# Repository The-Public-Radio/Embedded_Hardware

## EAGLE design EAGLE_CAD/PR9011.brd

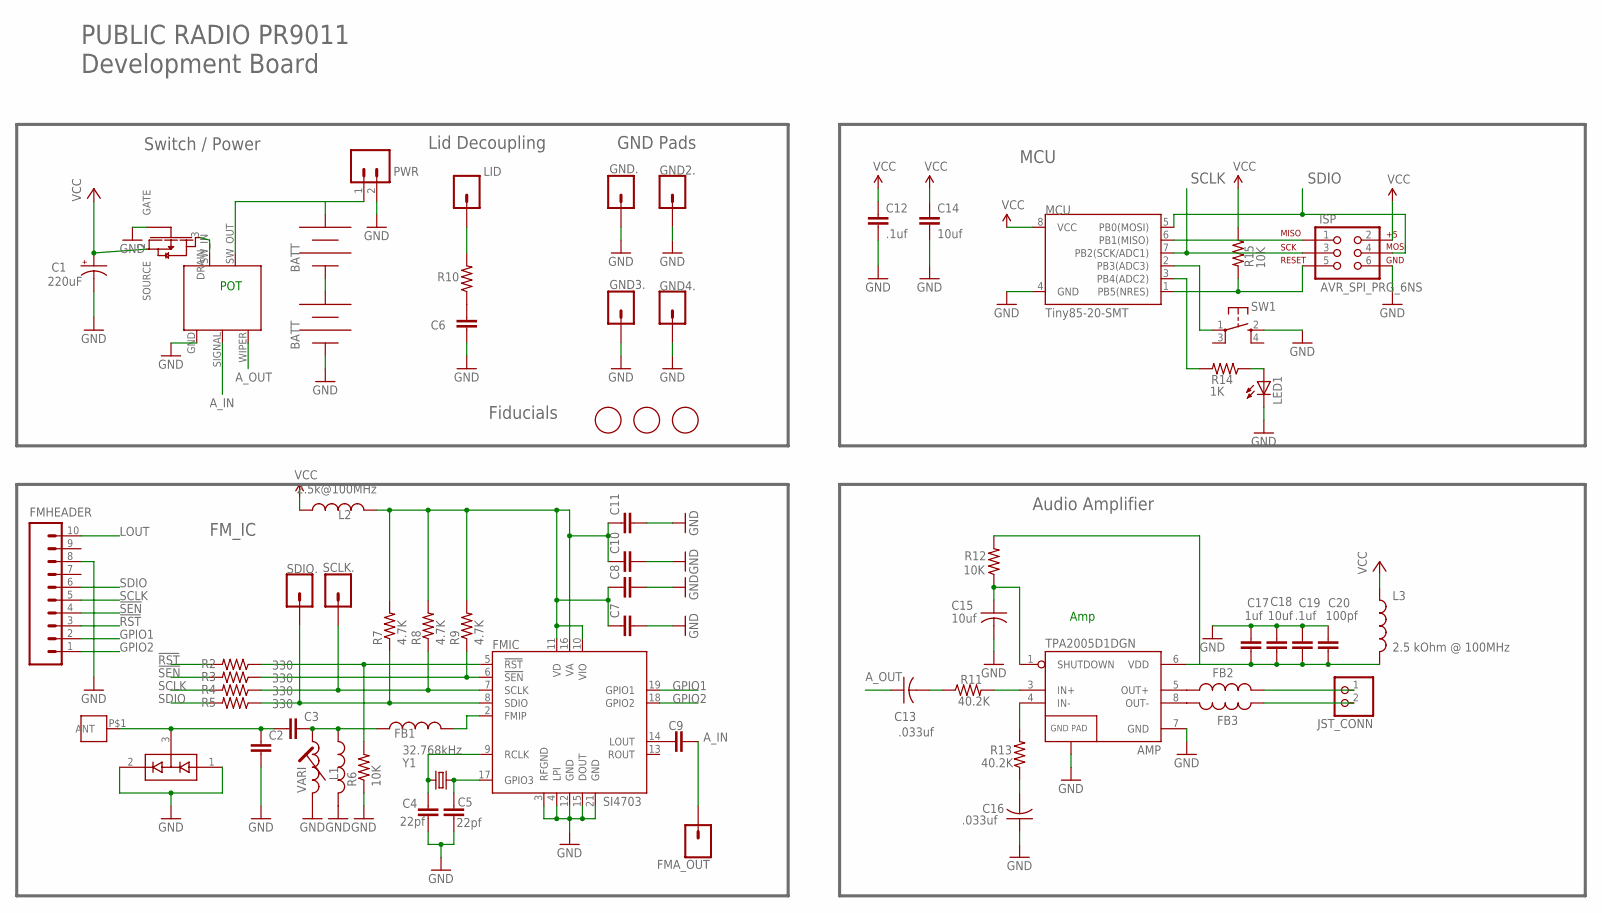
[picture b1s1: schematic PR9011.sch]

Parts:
AMP: TPA2005D1DGN; POWER-SOP8
C1: 220uF; PANASONIC_C
C2, C3, C7, C9: 1.0uF; 0805
C4, C5: 22pf; 0805
C6: CAP0805; 0805
C8: .1uF; 0805
C10: 22nF; 0805
C11: 4.7uF; 0805
C12, C19: .1uf; 0805
C13, C16: .033uf; C0603
C14, C18: 10uf; 0805
C15: 10uf; C0603
C17: 1uf; 0805
C20: 100pf; 0805
D1: BAV99; SOT23-3
FB1, FB2, FB3: INDUCTOR0805; 0805
FET1: SI2333DDS
FMA_OUT: M01PTH; 1X01
FMHEADER: M10LOCK; 1X10_LOCK
FMIC: SI4703; SPARKFUN_SI470X
GND2., GND3., GND4., GND.: M01PTH; 1X01
ISP: AVR_SPI_PRG_6NS; 2X3-NS
J1: M3_SCREW_POST
JP5, JP6: BK-92_MPD_AA_BATT_CLIP
JST_CONN: JST_2PIN-SMT-RA; JST-PH-2-SMT-RA
L1: INDUCTOR0805; 0805
L2: 2.5k@100MHz; 0603
L3: 2.5 kOhm @ 100MHz; 0603
LED1: LEDSML0603; SML0603
LID: M01PTH; 1X01
MCU: Tiny85-20-SMT; SO08-EIAJ
PWR: M02PTH3; 1X02_LONGPADS
R1: RV170SF_TAIWANA_POT_SW
R2, R3, R4, R5: 330; 0805
R6: 10K; 0805
R7, R8, R9: 4.7K; 0805
R10: RESISTOR0805-RES; 0805
R11, R13: 40.2K; R0603
R12, R15: 10K; R0603
R14: 1K; R0603
SCLK.: M01PTH; 1X01
SDIO.: M01PTH; 1X01
SW1: SPST_TACT-KMR2; KMR2
U$1, U$2, U$4: FIDUCIAL; FIDUCIAL_1MM
VARI: L-TRIM; 146/150
Y1: 32.768kHz; CRYSTAL-32KHZ-SMD

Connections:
3.3V: C7.1, C8.1, C10.1, C11.1, FMIC.10 (VIO), FMIC.11 (VD), FMIC.16 (VA), L2.2, R7.2, R8.2, R9.2
!RST-L: FMIC.5 (!RST), R2.1, R6.2
!SEN: FMHEADER.4, R3.2
!SEN-L: FMIC.6 (!SEN), R3.1, R9.1
A_IN: C9.2, FMA_OUT.1, R1.SIGNAL
A_OUT: C13.1, R1.WIPER
GND: AMP.7 (GND), AMP.9 (GND), C1.-, C2.2, C4.2, C5.2, C6.2, C7.2, C8.2, C10.2, C11.2, C12.2, C14.2, C15.2, C16.1, C17.1, C18.1, C19.1, C20.1, D1.1 (A1), D1.2 (C2), FET1.1 (GATE), FMHEADER.8, FMIC.3 (RFGND), FMIC.4 (LPI), FMIC.12 (GND), FMIC.15 (DOUT), FMIC.21 (GND), GND2..1, GND3..1, GND4..1, GND..1, ISP.6, JP6.NEG, JP6.NEG@2 (NEG), L1.2, LED1.C, MCU.4 (GND), PWR.2, R1.GND, R6.1, SW1.2 (S), VARI.P$1 (START)
GPIO1: FMHEADER.2, FMIC.19 (GPIO1)
GPIO2: FMHEADER.1, FMIC.18 (GPIO2)
LOUT: C9.1, FMHEADER.10, FMIC.14 (LOUT)
unnamed: C4.1, FMIC.9 (RCLK), Y1.X2 (2)
unnamed: C5.1, FMIC.17 (GPIO3), Y1.X1 (1)
unnamed: C13.2, R11.1
unnamed: AMP.3 (IN+), R11.2
unnamed: AMP.4 (IN-), R13.2
unnamed: FB1.2, FMIC.2 (FMIP)
unnamed: LED1.A, R14.1
unnamed: LID.1, R10.2
unnamed: FB2.2, JST_CONN.1 (2)
unnamed: MCU.2 (PB3(ADC3)), SW1.1
unnamed: MCU.3 (PB4(ADC2)), R14.2
unnamed: JP5.NEG, JP5.NEG@2 (NEG), JP6.POS, JP6.POS@2 (POS)
unnamed: C2.1, C3.1, D1.3 (COM), J1.P$1
unnamed: JP5.POS, JP5.POS@2 (POS), PWR.1, R1.SW_OUT
unnamed: C3.2, FB1.1, L1.1, VARI.P$2 (END)
unnamed: AMP.8 (OUT-), FB3.2
unnamed: AMP.6 (VDD), C17.2, C18.2, C19.2, C20.2, L3.2, R12.2
unnamed: AMP.5 (OUT+), FB2.1
unnamed: AMP.1 (SHUTDOWN), C15.1, R12.1
unnamed: C16.2, R13.1
unnamed: FET1.3 (DRAIN), R1.SW_IN
unnamed: C6.1, R10.1
OUT-: FB3.1, JST_CONN.2 (1)
PB5: ISP.5, MCU.1 (PB5(NRES)), R15.2
SCLK: FMHEADER.5, ISP.3, MCU.7 (PB2(SCK/ADC1)), R4.2
SCLK-L: FMIC.7 (SCLK), R4.1, R8.1, SCLK..1
SDIO: FMHEADER.6, ISP.4, MCU.5 (PB0(MOSI)), R5.2
SDIO-L: FMIC.8 (SDIO), R5.1, R7.1, SDIO..1
VCC: C1.+, C12.1, C14.1, FET1.2 (SOURCE), ISP.2, L2.1, L3.1, MCU.8 (VCC), R15.1

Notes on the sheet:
Amp
POT
FM_IC
Switch / Power
Lid Decoupling
Audio Amplifier
MCU
PUBLIC RADIO PR9011 Development Board
GND Pads
Fiducials

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
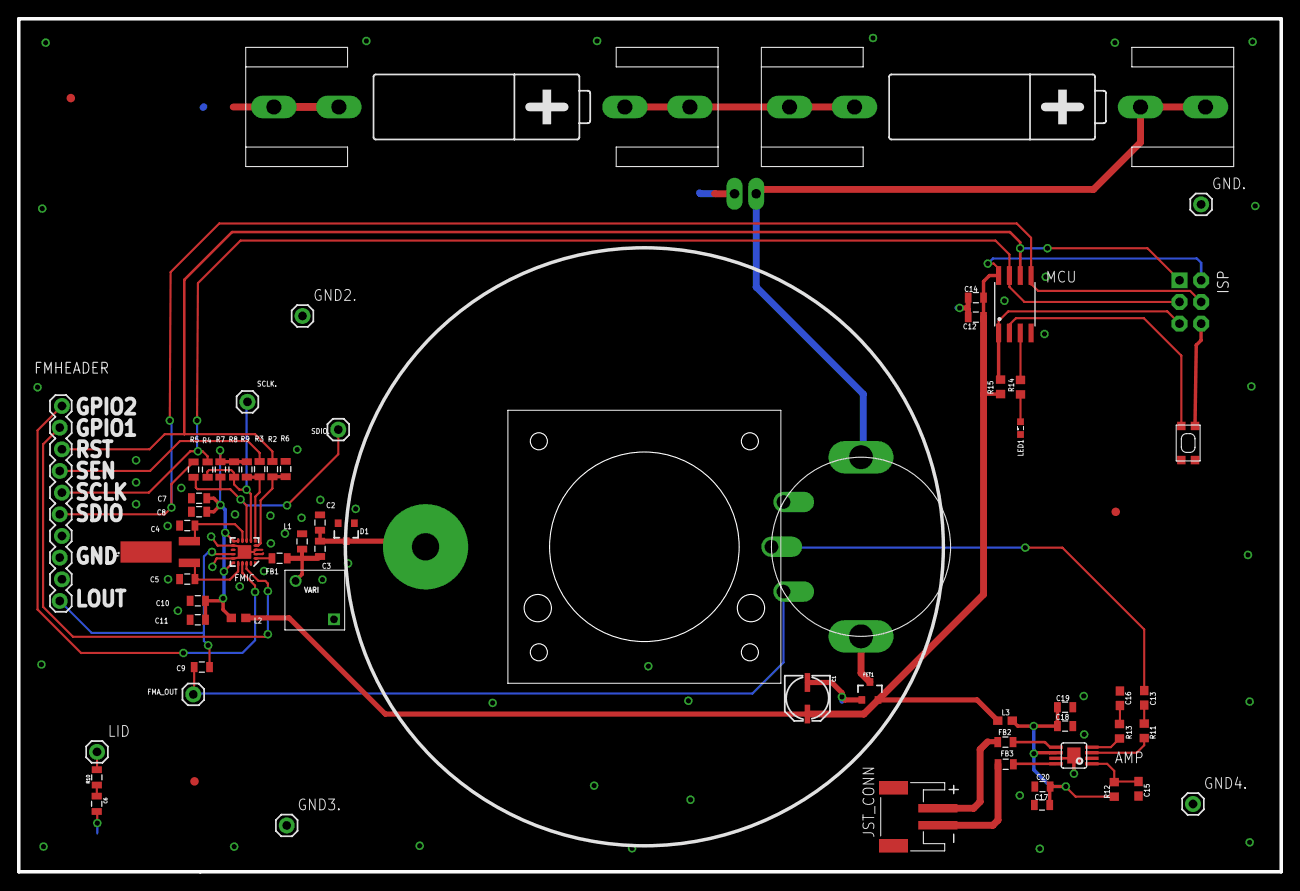
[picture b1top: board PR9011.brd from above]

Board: 2 copper layers, 148.0 x 100.0 mm, 69 parts (0 on the bottom side), 40 nets.

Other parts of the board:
SPEAKER: CE32A_FOR_JST

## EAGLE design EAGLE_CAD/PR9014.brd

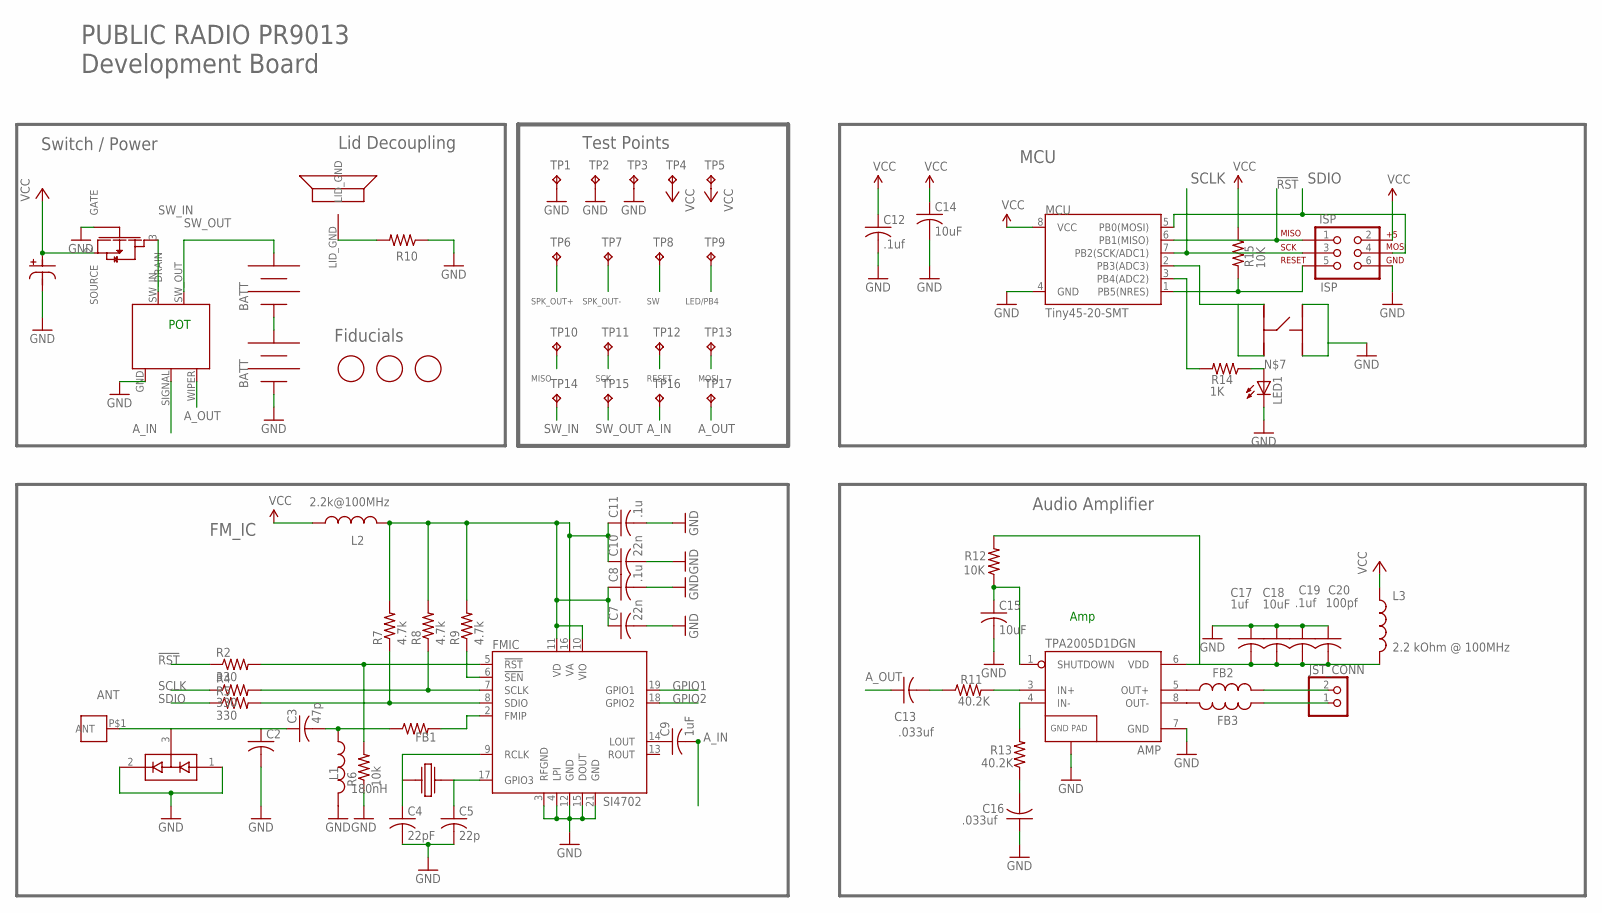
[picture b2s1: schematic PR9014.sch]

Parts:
AMP: TPA2005D1DGN; POWER-SOP8
C1: 220uF; NICHICON_SERIESUD
C2: C-USC0402; C0402
C3: 47p; C0402
C4: 22pF; C0402
C5: 22p; C0402
C7, C10: 22n; C0402
C8, C11: .1u; C0402
C9: 1uF; C0402
C12, C19: .1uf; C0402
C13, C16: .033uf; C0402
C14, C15, C18: 10uF; C0603
C17: 1uf; C0402
C20: 100pf; C0402
D1: BAV99; SOT23
FB1: R-US_R0402; R0402
FB2, FB3: INDUCTOR0805; 0805
FET2: AO3435
FMIC: SI4702; SI470X
ISP: ISP; 2X3-NS
J1: M3_SCREW_POST
JP5, JP6: BK-92_MPD_AA_BATT_CLIP
JST_CONN: JST_2PIN-SMT-RA; JST-PH-2-SMT-RA
L1: 180nH; 0805
L2: 2.2k@100MHz; C0402
L3: 2.2 kOhm @ 100MHz; C0402
LED1: LEDSML0603; SML0603
MCU: Tiny45-20-SMT; SO08-EIAJ
R1: RV170SF_TAIWANA_POT_SW
R2, R4, R5: 330; R0402
R6: 10k; R0402
R7, R8, R9: 4.7k; R0402
R10: R-US_R0805; R0805
R11, R13: 40.2K; R0402
R12, R15: 10K; R0402
R14: 1K; R0402
SW1: C&K_PTS645; C&K_TACTILE_SWITCH
TP1, TP2, TP3, TP4, TP5, TP6, TP7, TP8, TP9, TP10, TP11, TP12, TP13, TP14, TP15, TP16, TP17: TPTP20R; TP20R
U$1: CE32A_FOR_JST
U$3, U$4, U$5: FIDUCIAL; FIDUCIAL_1MM
U$6: ABS25XTAL

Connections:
3.3V: C7.1, C8.1, C10.1, C11.1, FMIC.10 (VIO), FMIC.11 (VD), FMIC.16 (VA), L2.2, R7.2, R8.2, R9.2
!RST: ISP.1, MCU.6 (PB1(MISO)), R2.1, TP10.TP
!RST-L: FMIC.5 (!RST), R2.2, R6.2
!SEN-L: FMIC.6 (!SEN), R9.1
ANT: C2.1, C3.1, D1.3 (COM), J1.P$1
A_IN: C9.2, R1.SIGNAL, TP16.TP
A_OUT: C13.1, R1.WIPER, TP17.TP
GND: AMP.7 (GND), AMP.9 (GND), C1.P$2, C2.2, C4.2, C5.2, C7.2, C8.2, C10.2, C11.2, C12.2, C14.2, C15.2, C16.1, C17.1, C18.1, C19.1, C20.1, D1.1 (A1), D1.2 (C2), FET2.1 (GATE), FMIC.3 (RFGND), FMIC.4 (LPI), FMIC.12 (GND), FMIC.15 (DOUT), FMIC.21 (GND), ISP.6, JP6.NEG, JP6.NEG@2 (NEG), L1.2, LED1.C, MCU.4 (GND), R1.GND, R6.1, R10.1, SW1.P$1, SW1.P$2, TP1.TP, TP2.TP, TP3.TP
GPIO1: FMIC.19 (GPIO1)
GPIO2: FMIC.18 (GPIO2)
LED/PB4: MCU.3 (PB4(ADC2)), R14.2, TP9.TP
unnamed: C4.1, FMIC.9 (RCLK), U$6.P$1
unnamed: C13.2, R11.1
unnamed: AMP.3 (IN+), R11.2
unnamed: AMP.4 (IN-), R13.2
unnamed: FB1.2, FMIC.2 (FMIP)
unnamed: LED1.A, R14.1
unnamed: R10.2, U$1.LID_GND
unnamed: C9.1, FMIC.14 (LOUT)
unnamed: C5.1, FMIC.17 (GPIO3), U$6.P$4
unnamed: JP5.NEG, JP5.NEG@2 (NEG), JP6.POS, JP6.POS@2 (POS)
unnamed: C3.2, FB1.1, L1.1
unnamed: AMP.8 (OUT-), FB3.2
unnamed: AMP.6 (VDD), C17.2, C18.2, C19.2, C20.2, L3.2, R12.2
unnamed: AMP.5 (OUT+), FB2.1
unnamed: AMP.1 (SHUTDOWN), C15.1, R12.1
unnamed: C16.2, R13.1
RESET: ISP.5, MCU.1 (PB5(NRES)), R15.2, TP12.TP
SCLK: ISP.3, MCU.7 (PB2(SCK/ADC1)), R4.1, TP11.TP
SCLK-L: FMIC.7 (SCLK), R4.2, R8.1
SDIO: ISP.4, MCU.5 (PB0(MOSI)), R5.1, TP13.TP
SDIO-L: FMIC.8 (SDIO), R5.2, R7.1
SPK_OUT+: FB2.2, JST_CONN.2 (1), TP6.TP
SPK_OUT-: FB3.1, JST_CONN.1 (2), TP7.TP
SW: MCU.2 (PB3(ADC3)), SW1.P$3, SW1.P$4, TP8.TP
SW_IN: FET2.3 (DRAIN), R1.SW_IN, TP14.TP
SW_OUT: JP5.POS, JP5.POS@2 (POS), R1.SW_OUT, TP15.TP
VCC: C1.P$1, C12.1, C14.1, FET2.2 (SOURCE), ISP.2, L2.1, L3.1, MCU.8 (VCC), R15.1, TP4.TP, TP5.TP

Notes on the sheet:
Amp
POT
FM_IC
Switch / Power
Lid Decoupling
Audio Amplifier
MCU
PUBLIC RADIO PR9013 Development Board
Fiducials
Test Points
MISO
SCK
RESET
MOSI

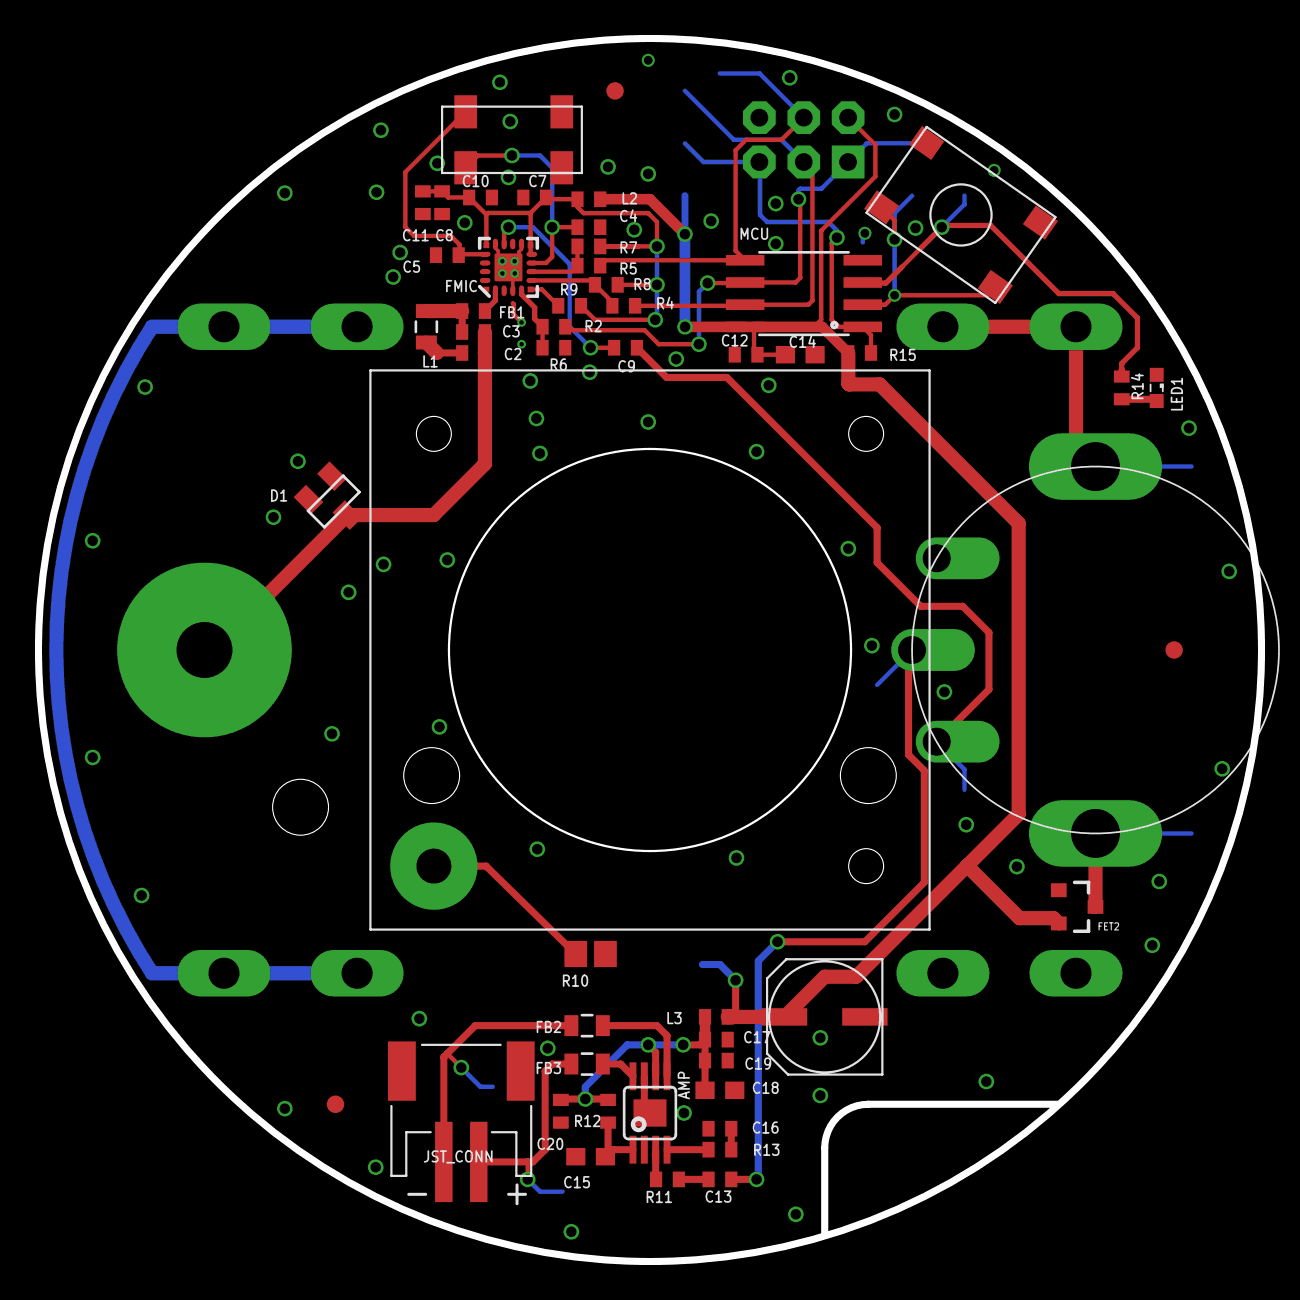
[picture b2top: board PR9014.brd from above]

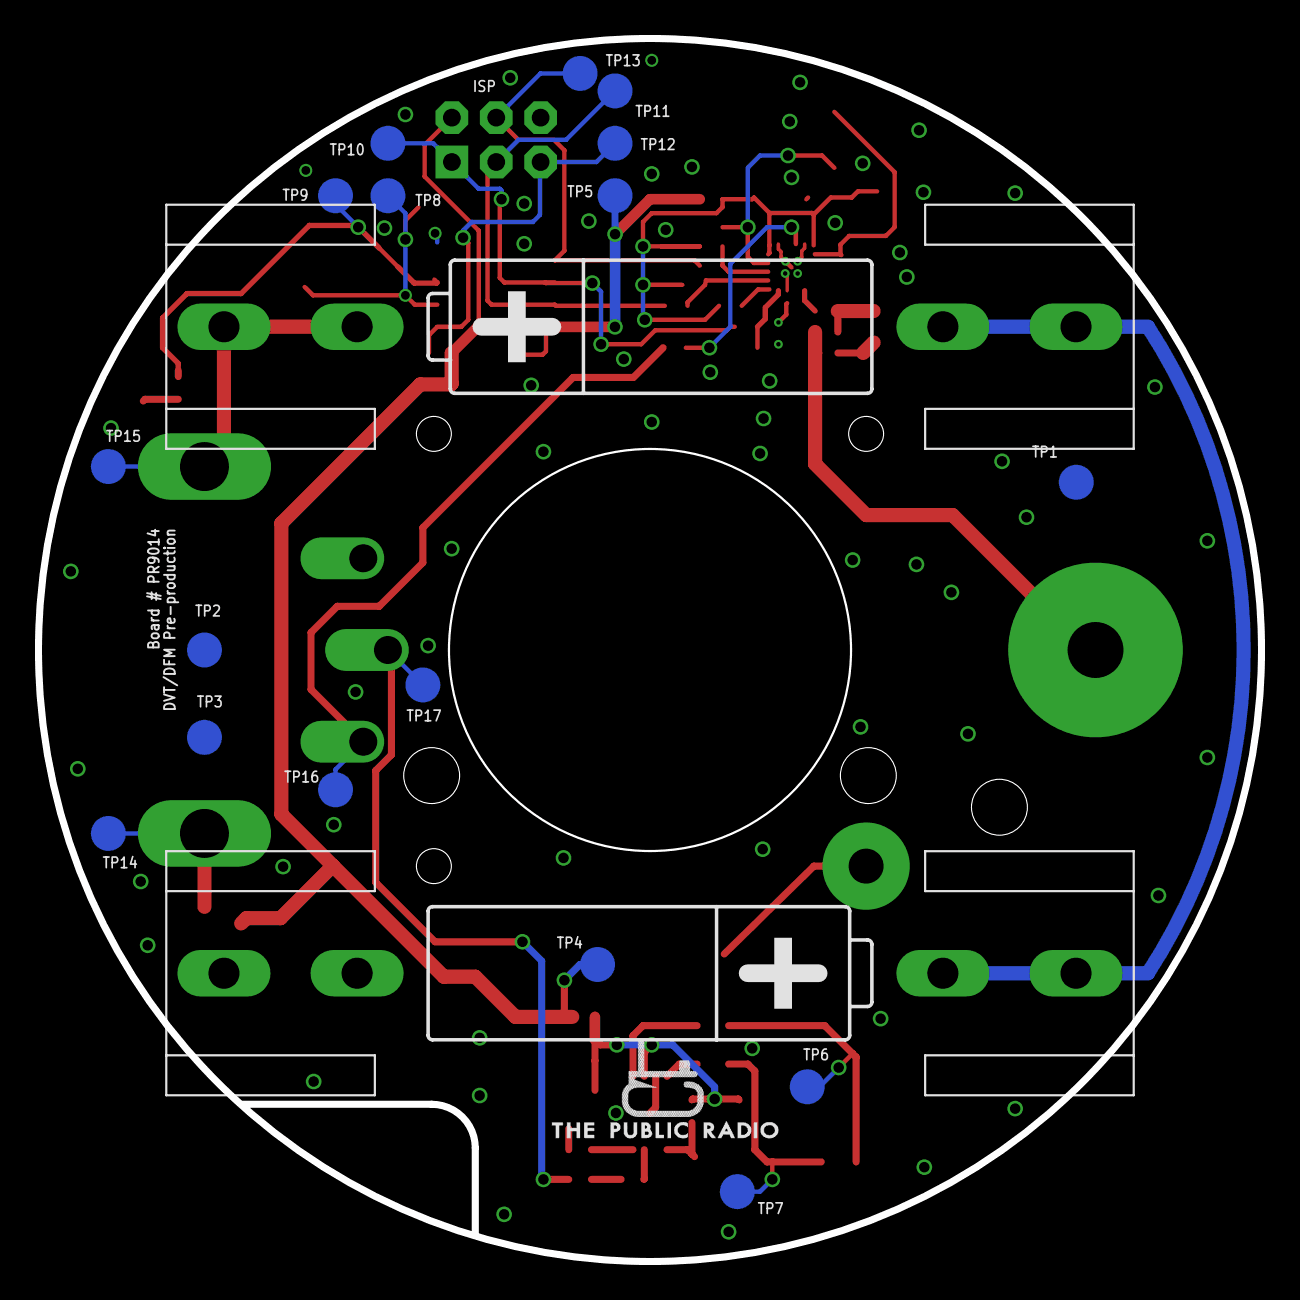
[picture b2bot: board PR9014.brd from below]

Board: 2 copper layers, 70.0 x 70.0 mm, 73 parts (20 on the bottom side), 36 nets.

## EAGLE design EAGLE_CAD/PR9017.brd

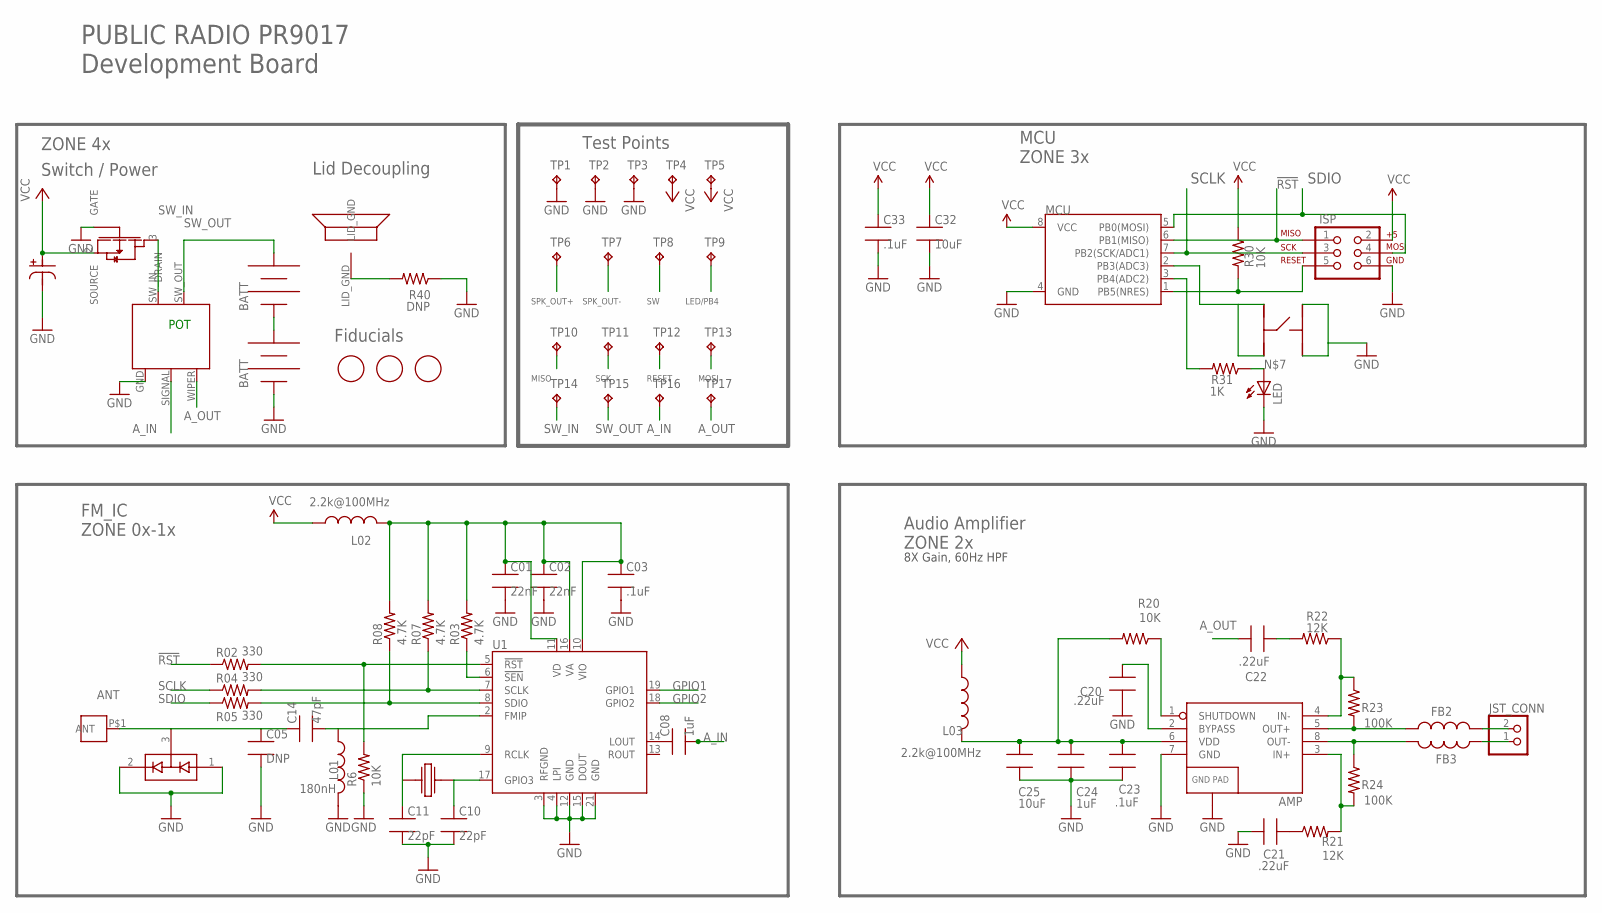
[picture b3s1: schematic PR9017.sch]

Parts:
AMP: TPA6203A1; 8-MSOP
ANT_MOUNT: DNP; M3_BOLT_HOLE
C01, C02: 22nF; 0603_CPL; VOLTAGE 16V; MFG_PN CL10B223KB8NNNC
C03, C23, C33: .1uF; 0603_CPL; VOLTAGE 16V; MFG_PN CL05B104KO5NNNC
C05: DNP; 0603_CPL; VOLTAGE 50V; MFG_PN DNP
C08, C24: 1uF; 0603_CPL; VOLTAGE 10V; MFG_PN CL10B105KP8NNNC
C10, C11: 22pF; 0603_CPL; VOLTAGE 50V; MFG_PN C1608C0G1H220J080AA
C14: 47pF; 0603_CPL; VOLTAGE 50V; MFG_PN CL10C470JB8NCNC
C20, C21, C22: .22uF; 0603_CPL; VOLTAGE 16V; MFG_PN C1608X7R1C224K080AC
C25, C32: 10uF; 0603_CPL; VOLTAGE 6.3V; MFG_PN CL10A106MQ8NNNC
C40: 220uF; NICHICON_UD_63; VOLTAGE 16V
D1: BAV99; SOT23_CPL; MFG_PN BAV99,215
FB2, FB3: L_SMT_0805_ADAFRUIT; 0805_ADAFRUIT; MFG_PN HI0805R800R-10
FET1: AO3435; SOT23_CPL; MFG_PN AO3435
ISP: AVR_SPI_PRG_6NS; 2X3-NS
JP5, JP6: BK-92_MPD_AA_BATT_CLIP; BK92_AA_BATT
JST_CONN: JST_2PIN-SMT-RA; JST-PH-2-SMT-RA
L01: 180nH; 0805_ADAFRUIT; MFG_PN AISC-0805-R18J-T
L02, L03: 2.2k@100MHz; 0603_CPL; MFG_PN HZ0603A222R-10
LED: LED; 0603_CPL; MFG_PN LY R976-PS-36
MARK1, MARK2, MARK3: FIDUCIAL; FIDUCIAL_1MM
MCU: ATTINY45TINY45-20-SMT; 8-SOIC
R1: RV170SF_TAIWANA_POT_SW; RV170SF_SW_POT
R02, R04, R05: 330; 0603_CPL; MFG_PN MCR03ERTJ331
R03, R07, R08: 4.7K; 0603_CPL; MFG_PN ERJ-3EKF4701V
R6, R20, R30: 10K; 0603_CPL; MFG_PN ERJ-3GEYJ103V
R21, R22: 12K; 0603_CPL; MFG_PN RMCF0603FT12K0
R23, R24: 100K; 0603_CPL; MFG_PN RMCF0603FT100K
R31: 1K; 0603_CPL; MFG_PN ERJ-3EKF1001V
R40: DNP; 0603_CPL; MFG_PN ERJ-3GEY0R00V
SPKR_PLACE: DNP; PR2023_SPKR_PLACE
SW1: C&K_PTS645; C&K_PTS645_SMT
TP1, TP2, TP3, TP4, TP5, TP6, TP7, TP8, TP9, TP10, TP11, TP12, TP13, TP14, TP15, TP16, TP17: TPTP20R; TP20R
U1: SI4702-C19-GMR; SI470X_20_QFN
X1: ABS25XTAL; 4-SOJ

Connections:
3.3V: C01.1, C02.1, C03.1, L02.2, R03.2, R07.2, R08.2, U1.10 (VIO), U1.11 (VD), U1.16 (VA)
!RST: ISP.1, MCU.6 (PB1(MISO)), R02.1, TP10.TP
!RST-L: R02.2, R6.2, U1.5 (!RST)
!SEN-L: R03.1, U1.6 (!SEN)
ANT: ANT_MOUNT.P$1, C05.1, C14.1, D1.3 (COM)
A_IN: C08.2, R1.SIGNAL, TP16.TP
A_OUT: C22.2, R1.WIPER, TP17.TP
GND: AMP.7 (GND), AMP.9 (GND), C01.2, C02.2, C03.2, C05.2, C10.2, C11.2, C20.1, C21.1, C23.2, C24.2, C25.2, C32.2, C33.2, C40.P$2, D1.1 (A1), D1.2 (C2), FET1.1 (GATE), ISP.6, JP6.NEG, JP6.NEG@2 (NEG), L01.2, LED.2 (C), MCU.4 (GND), R1.GND, R6.1, R40.1, SW1.P$1, SW1.P$2, TP1.TP, TP2.TP, TP3.TP, U1.3 (RFGND), U1.4 (LPI), U1.12 (GND), U1.15 (DOUT), U1.21 (GND)
GPIO1: U1.19 (GPIO1)
GPIO2: U1.18 (GPIO2)
LED/PB4: MCU.3 (PB4(ADC2)), R31.2, TP9.TP
unnamed: C11.1, U1.9 (RCLK), X1.P$1
unnamed: AMP.6 (VDD), C23.1, C24.1, C25.1, L03.2, R20.2
unnamed: C22.1, R22.2
unnamed: AMP.5 (OUT+), FB2.1, R23.2
unnamed: AMP.3 (IN+), R21.2, R24.2
unnamed: LED.1 (A), R31.1
unnamed: R40.2, SPKR_PLACE.LID_GND
unnamed: C08.1, U1.14 (LOUT)
unnamed: C10.1, U1.17 (GPIO3), X1.P$4
unnamed: AMP.8 (OUT-), FB3.2, R24.1
unnamed: AMP.2 (BYPASS), C20.2
unnamed: JP5.NEG, JP5.NEG@2 (NEG), JP6.POS, JP6.POS@2 (POS)
unnamed: AMP.4 (IN-), R22.1, R23.1
unnamed: C14.2, L01.1, U1.2 (FMIP)
unnamed: AMP.1 (SHUTDOWN), R20.1
unnamed: C21.2, R21.1
RESET: ISP.5, MCU.1 (PB5(NRES)), R30.2, TP12.TP
SCLK: ISP.3, MCU.7 (PB2(SCK/ADC1)), R04.1, TP11.TP
SCLK-L: R04.2, R07.1, U1.7 (SCLK)
SDIO: ISP.4, MCU.5 (PB0(MOSI)), R05.1, TP13.TP
SDIO-L: R05.2, R08.1, U1.8 (SDIO)
SPK_OUT+: FB2.2, JST_CONN.2 (1), TP6.TP
SPK_OUT-: FB3.1, JST_CONN.1 (2), TP7.TP
SW: MCU.2 (PB3(ADC3)), SW1.P$3, SW1.P$4, TP8.TP
SW_IN: FET1.3 (DRAIN), R1.SW_IN, TP14.TP
SW_OUT: JP5.POS, JP5.POS@2 (POS), R1.SW_OUT, TP15.TP
VCC: C32.1, C33.1, C40.P$1, FET1.2 (SOURCE), ISP.2, L02.1, L03.1, MCU.8 (VCC), R30.1, TP4.TP, TP5.TP

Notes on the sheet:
POT
FM_IC ZONE 0x-1x
Switch / Power
Lid Decoupling
Audio Amplifier ZONE 2x
MCU ZONE 3x
PUBLIC RADIO PR9017 Development Board
Fiducials
Test Points
MISO
SCK
RESET
MOSI
8X Gain, 60Hz HPF
ZONE 4x

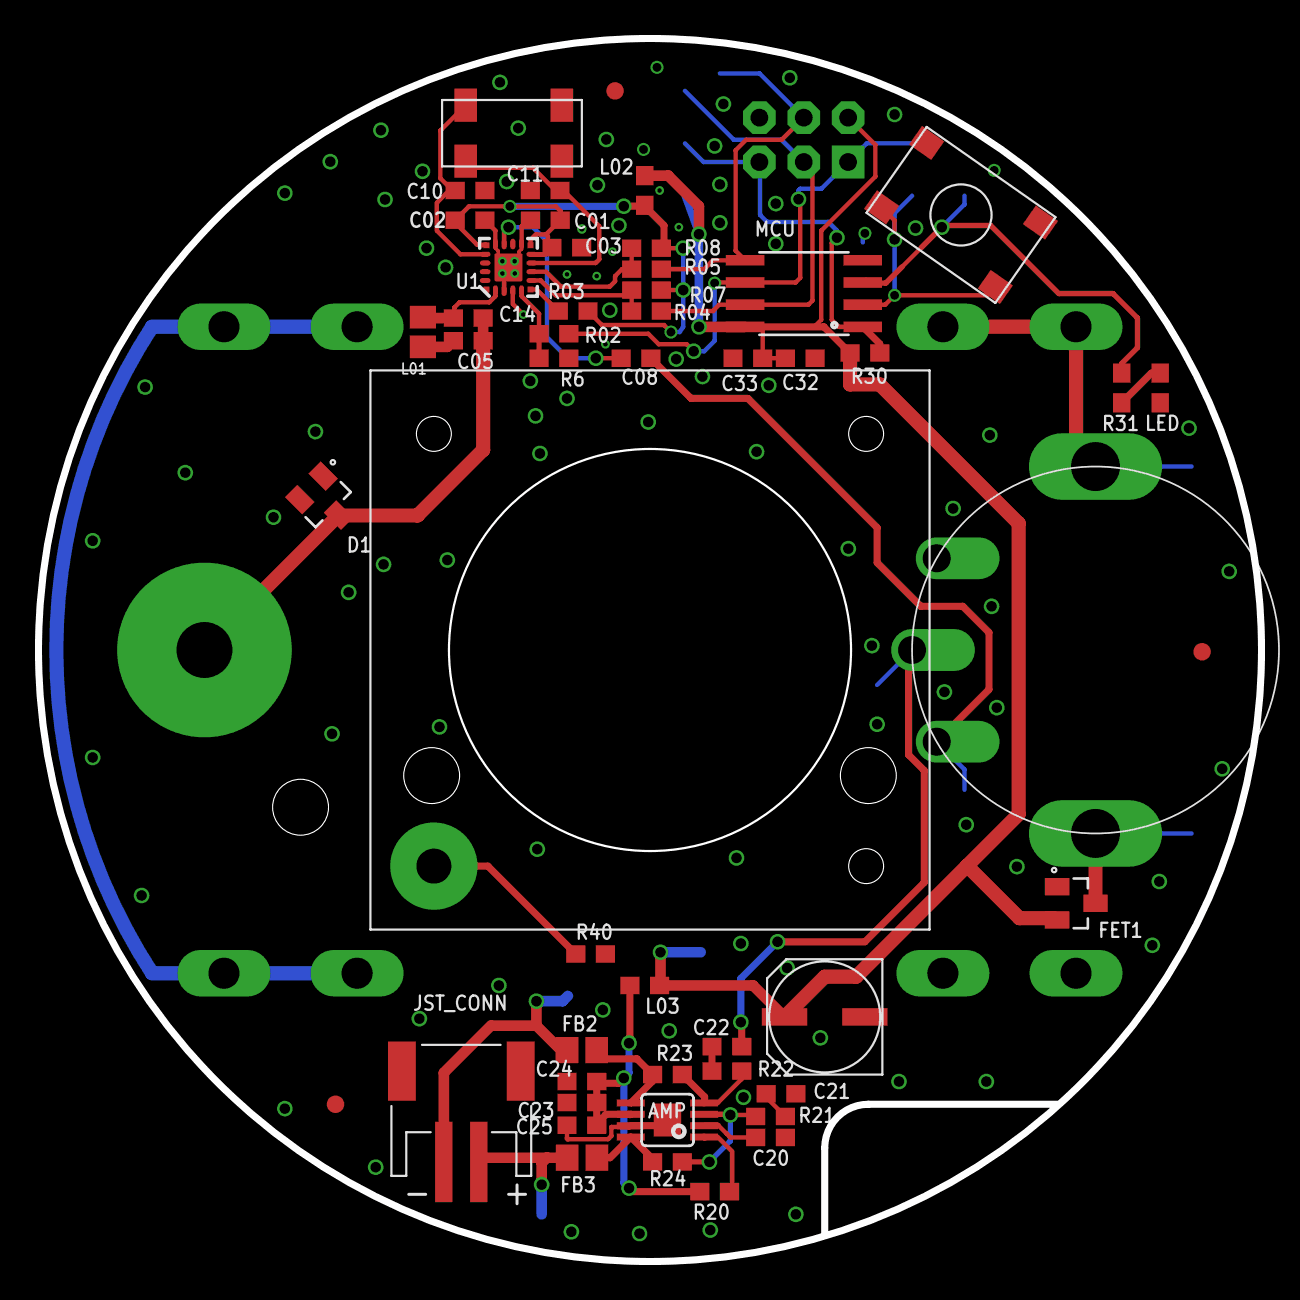
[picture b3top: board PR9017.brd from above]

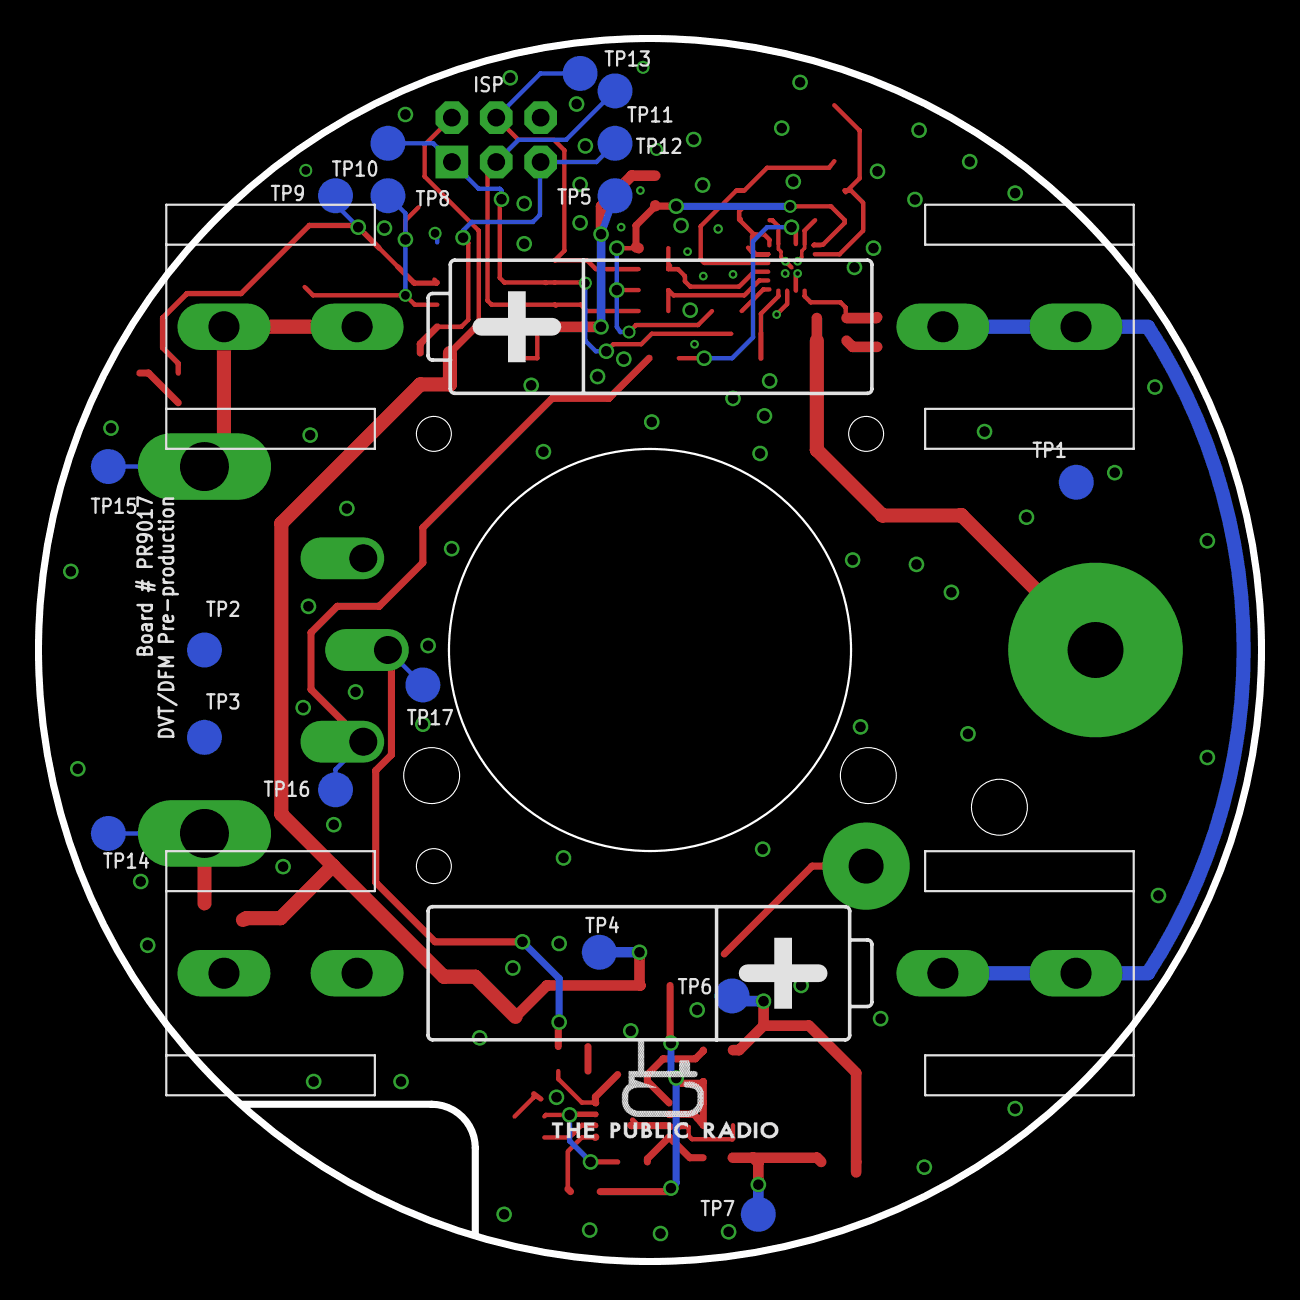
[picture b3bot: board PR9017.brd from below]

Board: 2 copper layers, 70.0 x 70.0 mm, 72 parts (20 on the bottom side), 36 nets.

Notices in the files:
parts and their libraries:
SparkFun-Connectors: Licensing: CC v3.0 Share-Alike You are welcome to use this library for commercial purposes.
SparkFun-DigitalIC: Licensing: Creative Commons ShareAlike 4.0 International - https://creativecommons.org/licenses/by-sa/4.0
